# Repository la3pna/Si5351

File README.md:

Si5351
======

Si5351 things

Cadsoft eagle shematics and board layout for the Si5351A backpack. 

Load ATmega32U4 with Arduino bootloader to upload via USB. 

Boards avaible at https://oshpark.com/shared_projects/lqFvJlVT

Mounting tips:
The LCD is supposed to go on the microcontroller side. mount the large components like SMB connectors, crystal (if hole mounted) and pot on the backside of the board.

Arduino pinout:

D0    ENCODER A (Interrupt)

D1    ENCODER b (Interrupt)

D2    I2C SDA to Si5351A

D3    I2C SCI to Si5351A

D4    Extra

D5    Extra

D6    LCD D7

D7    ENCODER SWITCH (Interrupt)

D8    LCD D6

D9    LCD D5

D10   LCD D4

D11   LCD Enable

D12   LCD RS

D13   External LED

None of the analog pins are connected.

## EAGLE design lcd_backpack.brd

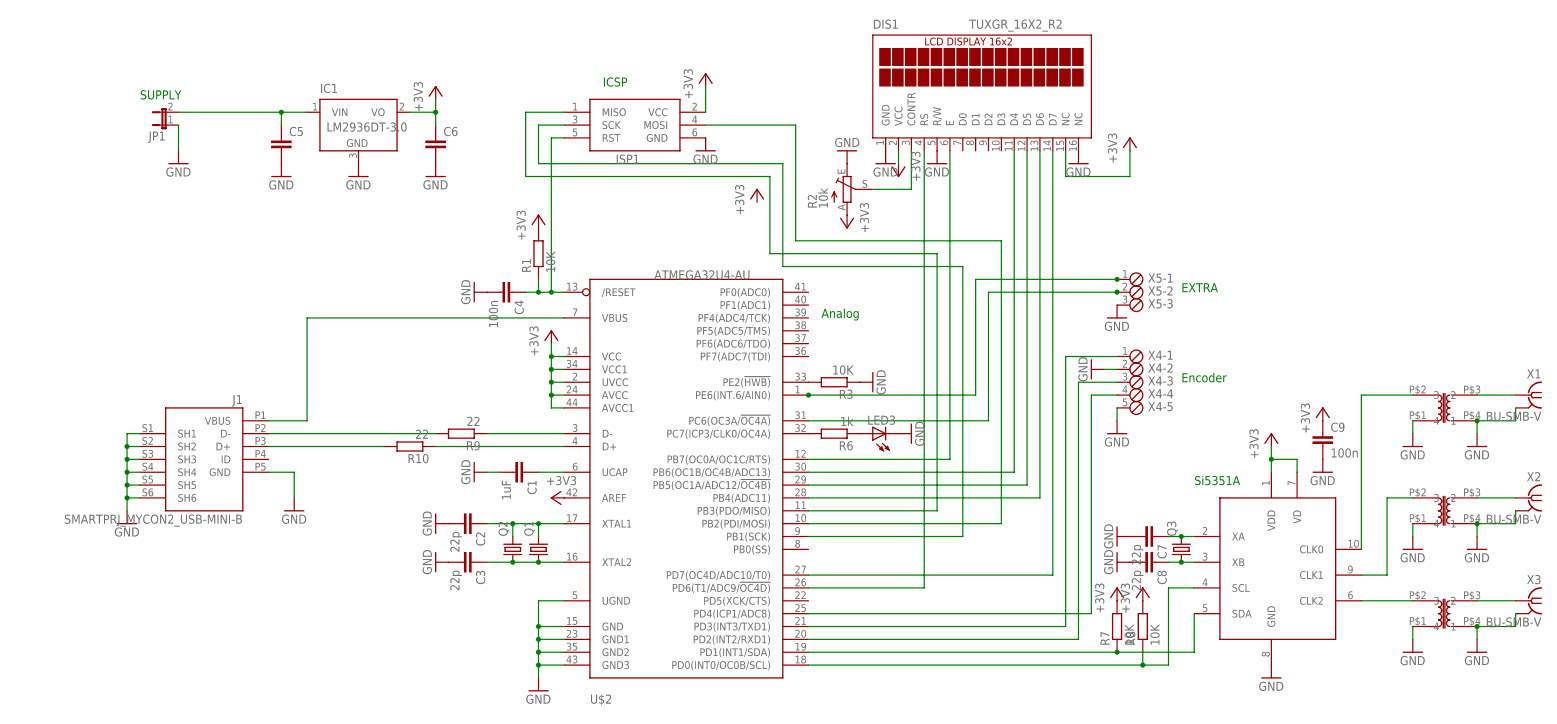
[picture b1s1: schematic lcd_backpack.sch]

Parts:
C1: 1uF; C0805
C2, C3, C7, C8: 22p; C0805
C4, C9: 100n; C0805
C5, C6: C-EUC0805; C0805
DIS1: TUXGR_16X2_R2
IC1: LM2936DT-3.0; TO252
ISP1: AVRISP-6; AVRISP
J1: SMARTPRJ_MYCON2_USB-MINI-B; SMARTPRJ_CON2_USB_MICRO_B_AT
JP1: JUMPER-2PTH_LOCK; 1X02_LOCK
LED3: LED3MM
Q1: CRYSTALHC49UP; HC49UP
Q2: CRYSTALHC49U-V; HC49U-V
Q3: CRYSTALCTS406; CTS406
R1, R3, R7, R8: 10K; M0805
R2: 10k; B25P
R6: 1k; M0805
R9, R10: 22; M0805
TR1, TR2, TR3: FT2402_TRAFO; 2402_TRAFO
U$1: SI5351; MSOP10
U$2: ATMEGA32U4-AU; TQFP44
X1, X2, X3: BU-SMB-V
X4: MPT5; 5POL254
X5: MPT3; 3POL254

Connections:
+3V3: C6.1, C9.1, DIS1.2 (VCC), DIS1.15 (NC), IC1.2 (VO), ISP1.2 (VCC), R1.2, R2.A, R7.2, R8.2, U$1.1 (VDD), U$1.7 (VD), U$2.2 (UVCC), U$2.14 (VCC), U$2.24 (AVCC), U$2.34 (VCC1), U$2.42 (AREF), U$2.44 (AVCC1)
GND: C1.2, C2.2, C3.2, C4.2, C5.2, C6.2, C7.2, C8.2, C9.2, DIS1.1 (GND), DIS1.5 (R/W), DIS1.16 (NC), IC1.3 (GND), ISP1.6 (GND), J1.P5 (GND), J1.S1 (SH1), J1.S2 (SH2), J1.S3 (SH3), J1.S4 (SH4), J1.S5 (SH5), J1.S6 (SH6), JP1.1, LED3.K (C), R2.E, R3.1, TR1.P$1 (1), TR1.P$4 (4), TR2.P$1 (1), TR2.P$4 (4), TR3.P$1 (1), TR3.P$4 (4), U$1.8 (GND), U$2.5 (UGND), U$2.15 (GND), U$2.23 (GND1), U$2.35 (GND2), U$2.43 (GND3), X1.2, X1.3 (2), X1.4 (2), X1.5 (2), X2.2, X2.3 (2), X2.4 (2), X2.5 (2), X3.2, X3.3 (2), X3.4 (2), X3.5 (2), X4.2, X4.5, X5.3
unnamed: J1.P3 (D+), R10.2
unnamed: J1.P2 (D-), R9.2
unnamed: J1.P1 (VBUS), U$2.7 (VBUS)
unnamed: DIS1.4 (RS), U$2.26 (PD6(T1/ADC9/!OC4D))
unnamed: C1.1, U$2.6 (UCAP)
unnamed: DIS1.6 (E), U$2.12 (PB7(OC0A/OC1C/RTS))
unnamed: C2.1, Q1.2, Q2.2, U$2.17 (XTAL1)
unnamed: C3.1, Q1.1, Q2.1, U$2.16 (XTAL2)
unnamed: C4.1, ISP1.5 (RST), R1.1, U$2.13 (/RESET)
unnamed: DIS1.3 (CONTR), R2.S
unnamed: DIS1.11 (D4), U$2.30 (PB6(OC1B/OC4B/ADC13))
unnamed: DIS1.12 (D5), U$2.29 (PB5(OC1A/ADC12/!OC4B))
unnamed: DIS1.13 (D6), U$2.28 (PB4(ADC11))
unnamed: DIS1.14 (D7), U$2.27 (PD7(OC4D/ADC10/T0))
unnamed: TR3.P$3 (3), X3.1
unnamed: C5.1, IC1.1 (VIN), JP1.2
unnamed: TR2.P$3 (3), X2.1
unnamed: TR1.P$3 (3), X1.1
unnamed: R8.1, U$1.4 (SCL), U$2.18 (PD0(INT0/OC0B/SCL))
unnamed: R7.1, U$1.5 (SDA), U$2.19 (PD1(INT1/SDA))
unnamed: ISP1.4 (MOSI), U$2.10 (PB2(PDI/MOSI))
unnamed: C8.1, Q3.1, U$1.3 (XB)
unnamed: C7.1, Q3.3 (2), U$1.2 (XA)
unnamed: TR1.P$2 (2), U$1.10 (CLK0)
unnamed: TR2.P$2 (2), U$1.9 (CLK1)
unnamed: TR3.P$2 (2), U$1.6 (CLK2)
unnamed: R3.2, U$2.33 (PE2(!HWB))
unnamed: U$2.20 (PD2(INT2/RXD1)), X4.3
unnamed: U$2.21 (PD3(INT3/TXD1)), X4.1
unnamed: U$2.25 (PD4(ICP1/ADC8)), X4.4
unnamed: U$2.31 (PC6(OC3A/!OC4A)), X5.2
unnamed: U$2.1 (PE6(INT.6/AIN0)), X5.1
unnamed: ISP1.3 (SCK), U$2.9 (PB1(SCK))
unnamed: ISP1.1 (MISO), U$2.11 (PB3(PDO/MISO))
unnamed: R6.2, U$2.32 (PC7(ICP3/CLK0/OC4A))
unnamed: LED3.A, R6.1
unnamed: R9.1, U$2.3 (D-)
unnamed: R10.1, U$2.4 (D+)

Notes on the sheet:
Encoder
EXTRA
Analog
SUPPLY
ICSP
Si5351A

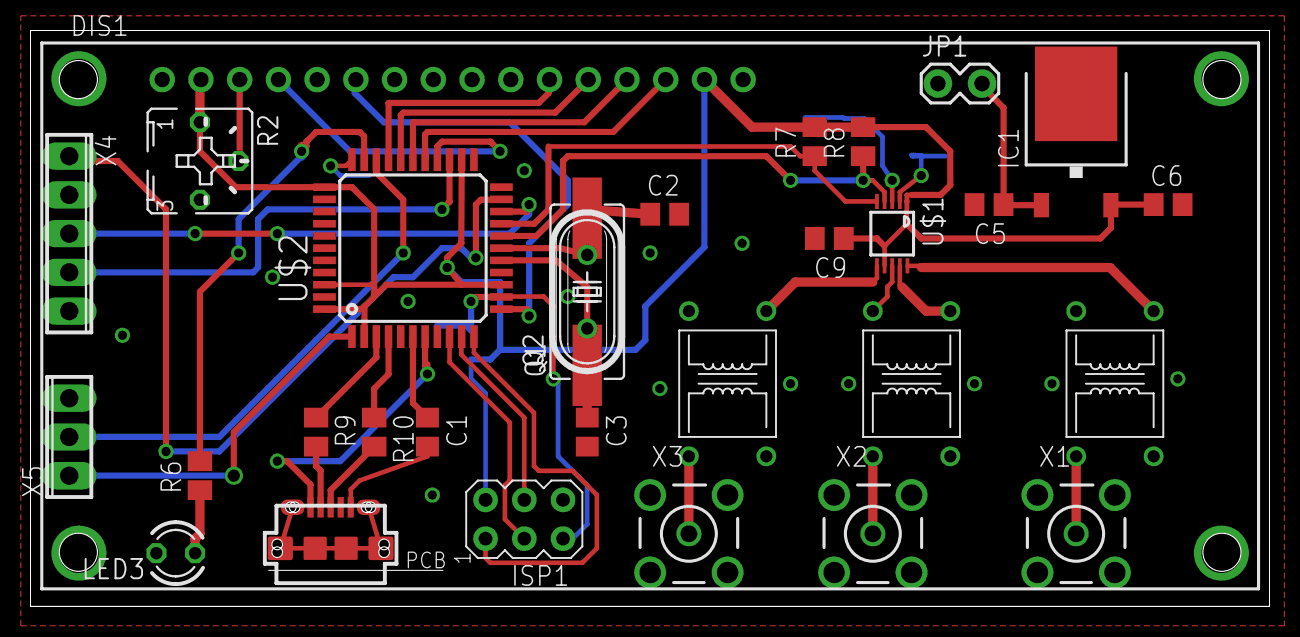
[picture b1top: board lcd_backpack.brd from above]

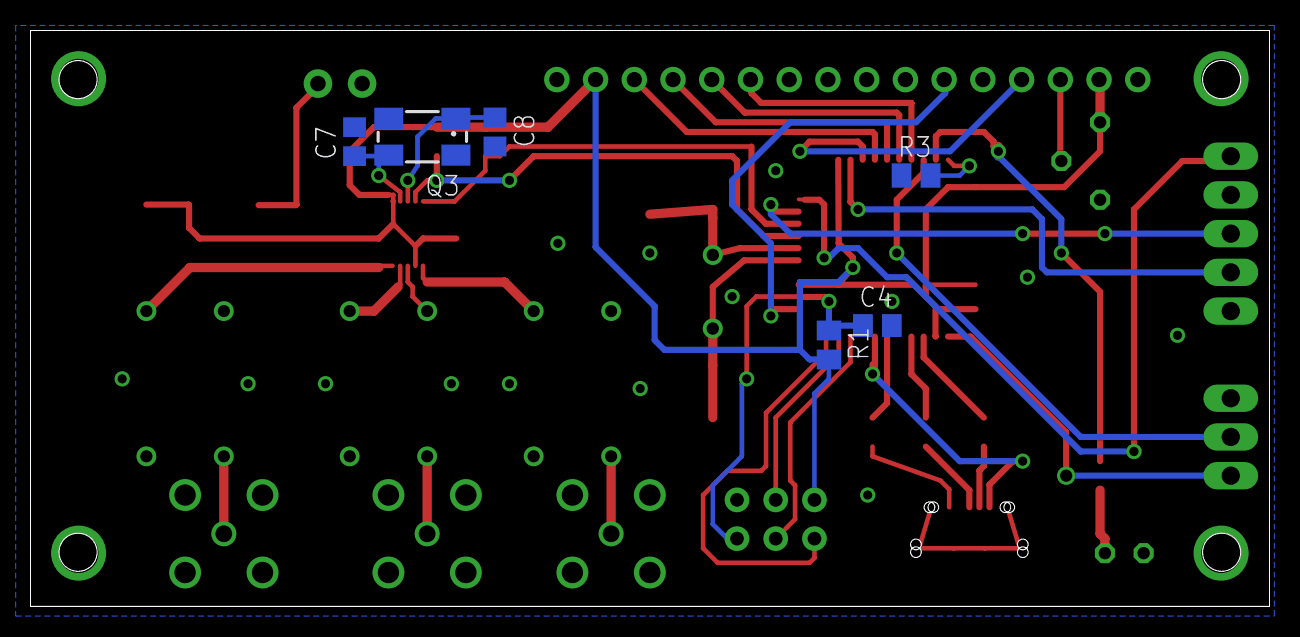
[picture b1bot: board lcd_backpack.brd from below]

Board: 2 copper layers, 81.3 x 37.8 mm, 36 parts (6 on the bottom side), 40 nets.

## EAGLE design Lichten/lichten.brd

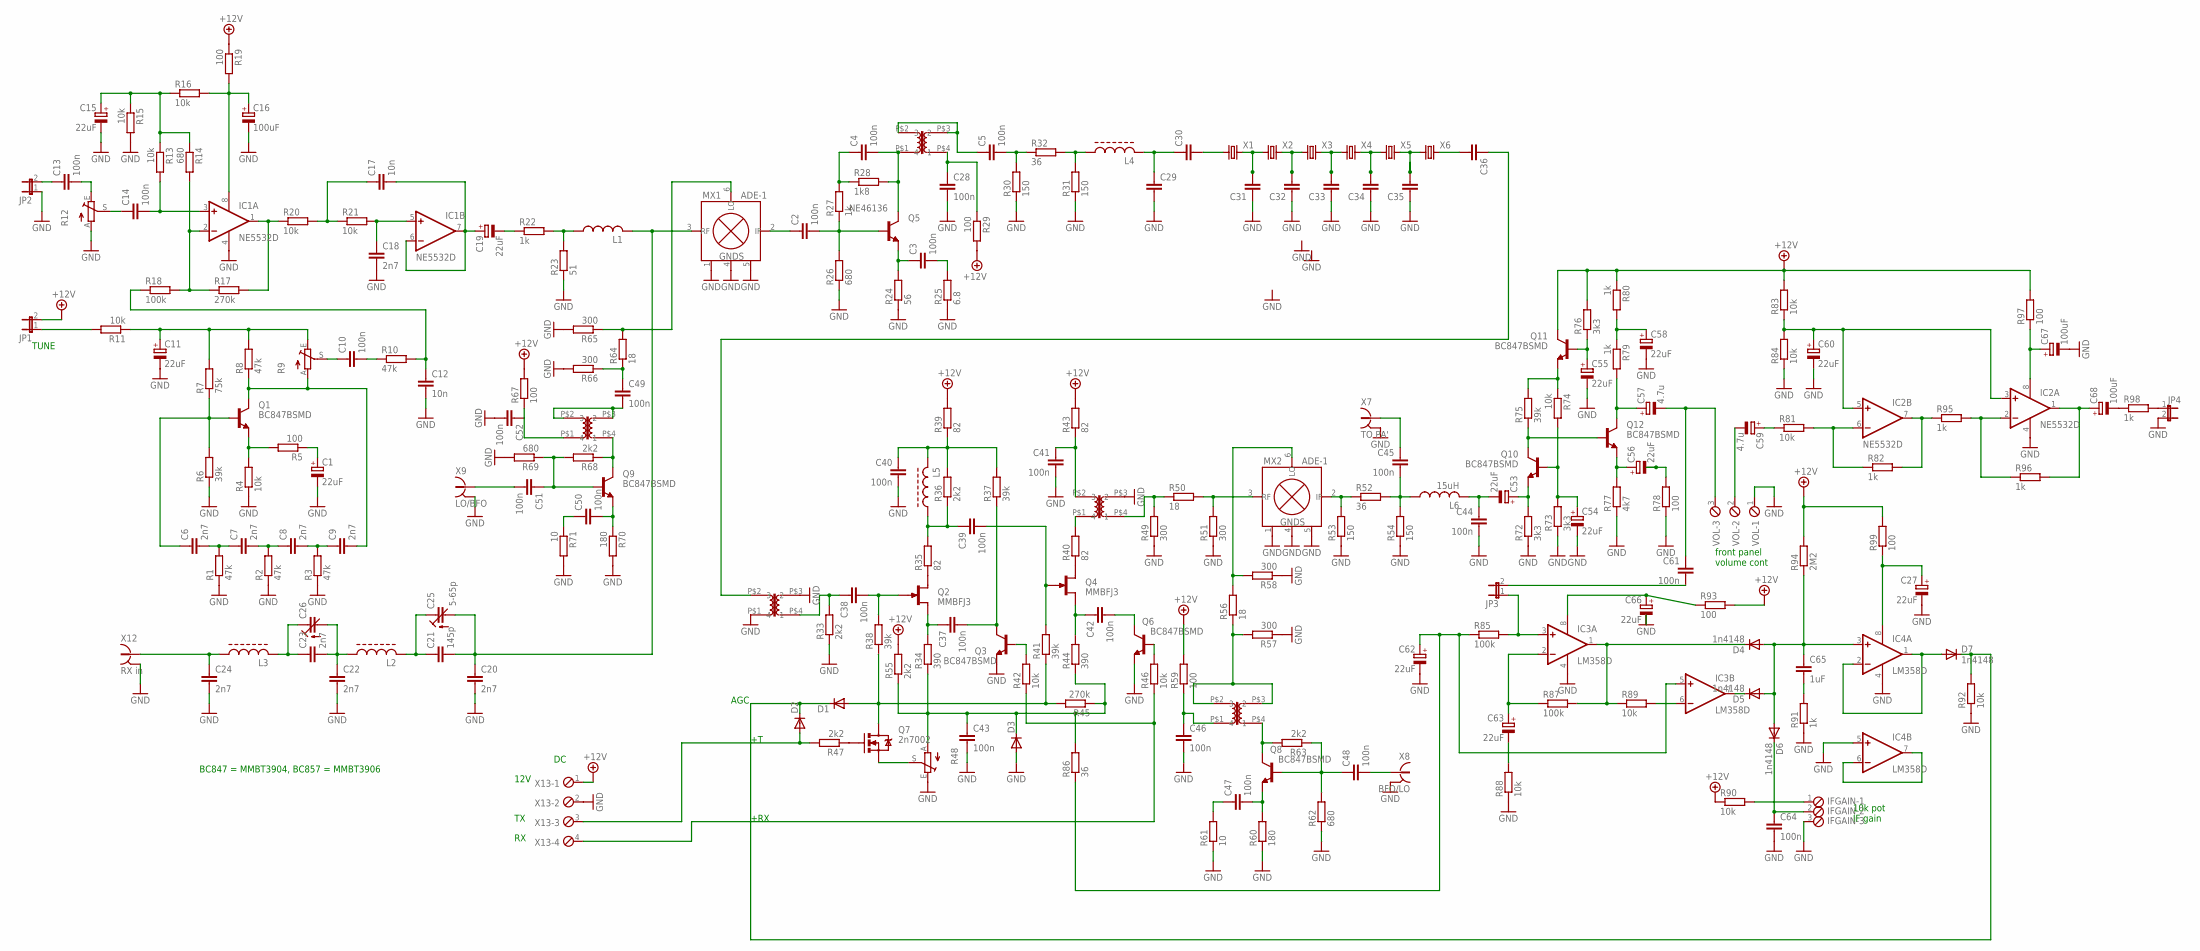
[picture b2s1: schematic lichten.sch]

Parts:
C1, C11, C15, C19, C27, C53, C54, C55, C56, C58, C60, C62, C63, C66: 22uF; PANASONIC_B
C2, C3, C4, C5, C10, C13, C14, C28, C37, C38, C39, C40, C41, C42, C43, C44, C45, C46, C47, C48, C49, C50, C51, C52, C61, C64: 100n; C1206K
C6, C7, C8, C9, C18, C20, C22, C23, C24: 2n7; C1206K
C12, C17: 10n; C1206K
C16, C67, C68: 100uF; PANASONIC_B
C21: 145p; C1206K
C25: 5-65p; CTRIM3050.505
C26: C-TRIMM3050.505; CTRIM3050.505
C29, C30, C31, C32, C33, C34, C35, C36: C-EUC1206K; C1206K
C57, C59: 4.7u; PANASONIC_B
C65: 1uF; C1206K
D1, D2, D3: DIODE-SOD80C; SOD80C
D4, D5, D6, D7: 1n4148; SOD80C
IC1, IC2: NE5532D; SO08
IC3, IC4: LM358D; SO08
IFGAIN: MPT3; 3POL254
JP1, JP2, JP3, JP4: JP1E; JP1
L1: L-US6000-XXX-RC; 6000-XXXX-RC
L2, L3, L4, L5: L-T37-UP
L6: 15uH; 6000-XXXX-RC
MX1, MX2: ADE-1; CD636
Q1, Q3, Q6, Q8, Q9, Q10, Q11, Q12: BC847BSMD; SOT23
Q2, Q4: MMBFJ3; SOT23
Q5: NE46136; SOT89-BCE
Q7: 2n7002; SOT23
R1, R2, R3, R8, R10: 47k; M1206
R4, R11, R13, R15, R16, R20, R21, R42, R46, R74, R81, R83, R84, R88, R89, R90, R92: 10k; M1206
R5, R19, R29, R59, R67, R78, R93, R97, R99: 100; M1206
R6, R37, R38, R41, R75: 39k; M1206
R7: 75k; M1206
R9, R12, R48: TRIM_EU-B25P; B25P
R14, R26, R62, R69: 680; M1206
R17, R45: 270k; M1206
R18, R85, R87: 100k; M1206
R22, R27, R79, R80, R82, R91, R95, R96, R98: 1k; M1206
R23: 51; M1206
R24: 56; M1206
R25: 6.8; M1206
R28: 1k8; M1206
R30, R31, R53, R54: 150; M1206
R32, R52, R86: 36; M1206
R33, R36, R47, R55, R63, R68: 2k2; M1206
R34, R44: 390; M1206
R35, R39, R40, R43: 82; M1206
R49, R51, R57, R58, R65, R66: 300; M1206
R50, R56, R64: 18; M1206
R60, R70: 180; M1206
R61, R71: 10; M1206
R72, R73, R76: 3k3; M1206
R77: 4k7; M1206
R94: 2M2; M1206
TR1, TR2, TR3, TR4, TR5: FT2402_TRAFO; 2402_TRAFO
VOL: MPT3; 3POL254
X1, X2, X3, X4, X5, X6: CRYSTALHC49S; HC49/S
X7: TO PA'; ST-SMB-V
X8: BFO/LO; ST-SMB-V
X9: LO/BFO; ST-SMB-V
X12: RX in; ST-SMB-V
X13: MPT4; 4POL254

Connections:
+12V: JP1.2, Q11.3 (C), R19.1, R29.2, R39.2, R43.2, R55.2, R59.2, R67.2, R76.2, R80.1, R83.2, R90.1, R93.2, R94.2, R97.2, R99.2, X13.1
GND: C1.-, C11.-, C12.2, C15.-, C16.-, C18.2, C20.2, C22.2, C24.2, C27.-, C28.2, C29.2, C31.1, C32.1, C33.1, C34.1, C35.1, C40.2, C41.2, C43.2, C44.2, C46.2, C52.2, C54.-, C55.-, C58.-, C60.-, C62.-, C64.2, C66.-, C67.-, D3.A, IC1.4 (V-), IC2.4 (V-), IC3.4 (V-), IC4.4 (V-), IC4.5 (+IN), IFGAIN.3, JP2.1, JP4.2, MX1.1 (GND), MX1.4 (GND), MX1.5 (GND), MX2.1 (GND), MX2.4 (GND), MX2.5 (GND), Q3.2 (E), Q6.2 (E), R1.1, R2.1, R3.1, R4.1, R6.1, R12.A, R15.2, R23.1, R24.1, R25.1, R26.1, R30.1, R31.1, R33.1, R48.E, R49.1, R51.1, R53.1, R54.1, R57.1, R58.1, R60.1, R61.1, R62.1, R65.2, R66.2, R69.2, R70.2, R71.2, R72.1, R73.1, R77.1, R78.1, R84.1, R88.1, R91.1, R92.1, TR2.P$1 (1), TR2.P$3 (3), TR3.P$3 (3), VOL.1, X7.2, X7.3 (2), X7.4 (2), X7.5 (2), X8.2, X8.3 (2), X8.4 (2), X8.5 (2), X9.2, X9.3 (2), X9.4 (2), X9.5 (2), X12.2, X12.3 (2), X12.4 (2), X12.5 (2), X13.2
unnamed: C20.1, C21.2, C25.2 (A), L1.2, MX1.3 (RF)
unnamed: C21.1, C25.1 (E), L2.2
unnamed: C22.1, C23.2, C26.2 (A), L2.1
unnamed: Q1.2 (E), R4.2, R5.2
unnamed: C1.+, R5.1
unnamed: C9.2, Q1.3 (C), R8.1, R9.A
unnamed: C8.2, C9.1, R3.2
unnamed: C7.2, C8.1, R2.2
unnamed: C6.2, C7.1, R1.2
unnamed: C6.1, Q1.1 (B), R6.2, R7.1
unnamed: C11.+, R7.2, R8.2, R9.E, R11.1
unnamed: C10.1, R9.S
unnamed: C10.2, R10.1
unnamed: C14.1, R12.S
unnamed: JP1.1, R11.2
unnamed: C12.1, R10.2, R18.1
unnamed: C13.2, R12.E
unnamed: C14.2, IC1.3 (+IN), R13.2
unnamed: C15.+, R13.1, R14.1, R15.1, R16.1
unnamed: IC1.2 (-IN), R14.2, R17.1, R18.2
unnamed: C23.1, C26.1 (E), L3.2
unnamed: IC1.1 (OUT), R17.2, R20.1
unnamed: C30.2, X1.1
unnamed: C13.1, JP2.2
unnamed: C24.1, L3.1, X12.1
unnamed: C2.1, MX1.2 (IF)
unnamed: C16.+, IC1.8 (V+), R16.2, R19.2
unnamed: C17.1, R20.2, R21.1
unnamed: C18.1, IC1.5 (+IN), R21.2
unnamed: C17.2, C19.+, IC1.6 (-IN), IC1.7 (OUT)
unnamed: C2.2, Q5.B, R26.2, R27.1
unnamed: C19.-, R22.1
unnamed: L1.1, R22.2, R23.2
unnamed: C3.1, Q5.E, R24.2
unnamed: C4.2, Q5.C, R28.2, TR1.P$1 (1)
unnamed: C4.1, R27.2, R28.1
unnamed: C5.1, TR1.P$2 (2), TR1.P$3 (3)
unnamed: C3.2, R25.2
unnamed: C28.1, R29.1, TR1.P$4 (4)
unnamed: C5.2, R30.2, R32.1
unnamed: L4.1, R31.2, R32.2
unnamed: C29.1, C30.1, L4.2
unnamed: C31.2, X1.2, X2.1
unnamed: C32.2, X2.2, X3.1
unnamed: C33.2, X3.2, X4.1
unnamed: C34.2, X4.2, X5.1
unnamed: C35.2, X5.2, X6.1
unnamed: C38.1, R33.2, TR2.P$4 (4)
unnamed: C36.2, X6.2
unnamed: C37.1, Q2.2 (S), R34.2
unnamed: Q2.1 (D), R35.1
unnamed: C39.1, L5.1, R35.2, R36.1
unnamed: C38.2, Q2.3 (G), R38.2
unnamed: C40.1, L5.2, R36.2, R37.2, R39.1
unnamed: C37.2, Q3.3 (C), R37.1
unnamed: C36.1, TR2.P$2 (2)
unnamed: C39.2, Q4.3 (G), R41.2
unnamed: Q4.1 (D), R40.1
unnamed: Q3.1 (B), R42.2
unnamed: D1.A, Q7.3 (D), R38.1, R41.1, R45.2
unnamed: R40.2, TR3.P$1 (1)
unnamed: C41.1, R43.1, TR3.P$2 (2)
unnamed: C42.1, Q4.2 (S), R44.2
unnamed: C42.2, Q6.3 (C)
unnamed: C68.+, IC2.1 (OUT), R96.2
unnamed: C43.1, D3.C, R34.1, R44.1, R45.1, R48.A, R55.1, R86.2
unnamed: Q6.1 (B), R46.2
unnamed: R42.1, R46.1, X13.4
unnamed: Q7.1 (G), R47.1
unnamed: D2.A, R47.2, X13.3
unnamed: Q7.2 (S), R48.S
unnamed: R49.2, R50.1, TR3.P$4 (4)
unnamed: MX2.3 (RF), R50.2, R51.2
unnamed: MX2.2 (IF), R52.1, R53.2
unnamed: C45.2, L6.1, R52.2, R54.2
unnamed: C44.1, C53.-, L6.2
unnamed: C45.1, X7.1
unnamed: C54.+, Q10.1 (B), R73.2, R74.2
unnamed: MX2.6 (LO), R56.2, R58.2
unnamed: R56.1, R57.2, TR4.P$2 (2), TR4.P$3 (3)
unnamed: Q8.3 (C), R63.2, TR4.P$4 (4)
unnamed: C46.1, R59.1, TR4.P$1 (1)
unnamed: C47.2, Q8.2 (E), R60.2
unnamed: C48.1, Q8.1 (B), R62.2, R63.1
unnamed: C47.1, R61.2
unnamed: C48.2, X8.1
unnamed: Q9.3 (C), R68.1, TR5.P$4 (4)
unnamed: C49.2, TR5.P$2 (2), TR5.P$3 (3)
unnamed: C49.1, R64.1, R66.1
unnamed: MX1.6 (LO), R64.2, R65.1
unnamed: C52.1, R67.1, TR5.P$1 (1)
unnamed: C51.1, Q9.1 (B), R68.2, R69.1
unnamed: C50.1, R71.1
unnamed: C50.2, Q9.2 (E), R70.1
unnamed: C51.2, X9.1
unnamed: C53.+, Q10.2 (E), R72.2
unnamed: C56.-, R78.2
unnamed: Q10.3 (C), Q12.1 (B), R75.1
unnamed: Q11.2 (E), R74.1, R75.2
unnamed: C55.+, Q11.1 (B), R76.1
unnamed: C67.+, IC2.8 (V+), R97.1
unnamed: C56.+, Q12.2 (E), R77.2
unnamed: C57.+, Q12.3 (C), R79.2
unnamed: C58.+, R79.1, R80.2
unnamed: C57.-, C61.1, VOL.3
unnamed: IC2.6 (-IN), R81.2, R82.1
unnamed: C59.-, VOL.2
unnamed: IC2.7 (OUT), R82.2, R95.1
unnamed: C59.+, R81.1
unnamed: C60.+, IC2.3 (+IN), IC2.5 (+IN), R83.1, R84.2
unnamed: C62.+, IC3.5 (+IN), R85.1, R86.1
unnamed: C63.-, R88.2
unnamed: C61.2, JP3.2
unnamed: C63.+, IC3.2 (-IN), R87.1
unnamed: D4.C, IC3.1 (OUT), R87.2, R89.1
unnamed: IC3.6 (-IN), R89.2
unnamed: C68.-, R98.1
unnamed: D5.C, IC3.7 (OUT)
unnamed: C65.1, D4.A, D5.A, D6.A, IC4.3 (+IN), R94.1
unnamed: IFGAIN.1, R90.2
unnamed: C64.1, D6.C, IFGAIN.2
unnamed: C65.2, R91.2
unnamed: D7.A, IC4.1 (OUT), IC4.2 (-IN)
unnamed: D1.C, D2.C, D7.C, R92.2
unnamed: C66.+, R93.1
unnamed: IC4.6 (-IN), IC4.7 (OUT)
unnamed: IC2.2 (-IN), R95.2, R96.1
unnamed: IC3.3 (+IN), JP3.1, R85.2
unnamed: JP4.1, R98.2
unnamed: C27.+, IC4.8 (V+), R99.1

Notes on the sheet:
BC847 = MMBT3904, BC857 = MMBT3906
TUNE
+RX
AGC
front panel volume cont
10k pot IF gain
12V

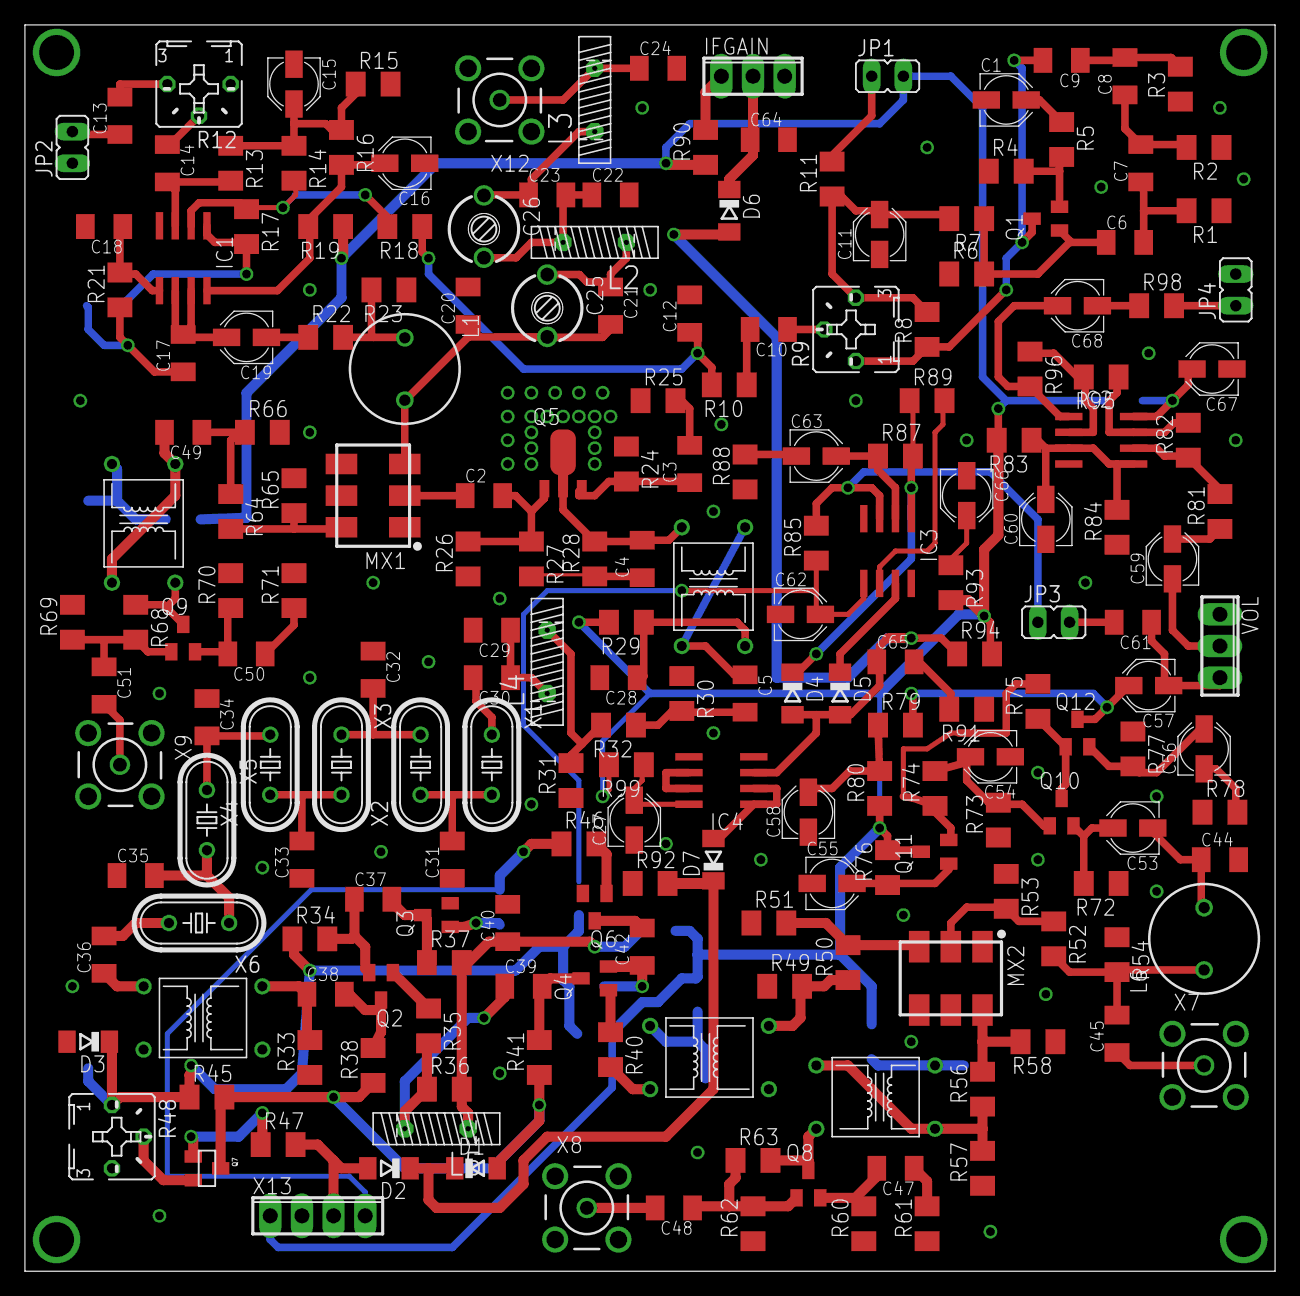
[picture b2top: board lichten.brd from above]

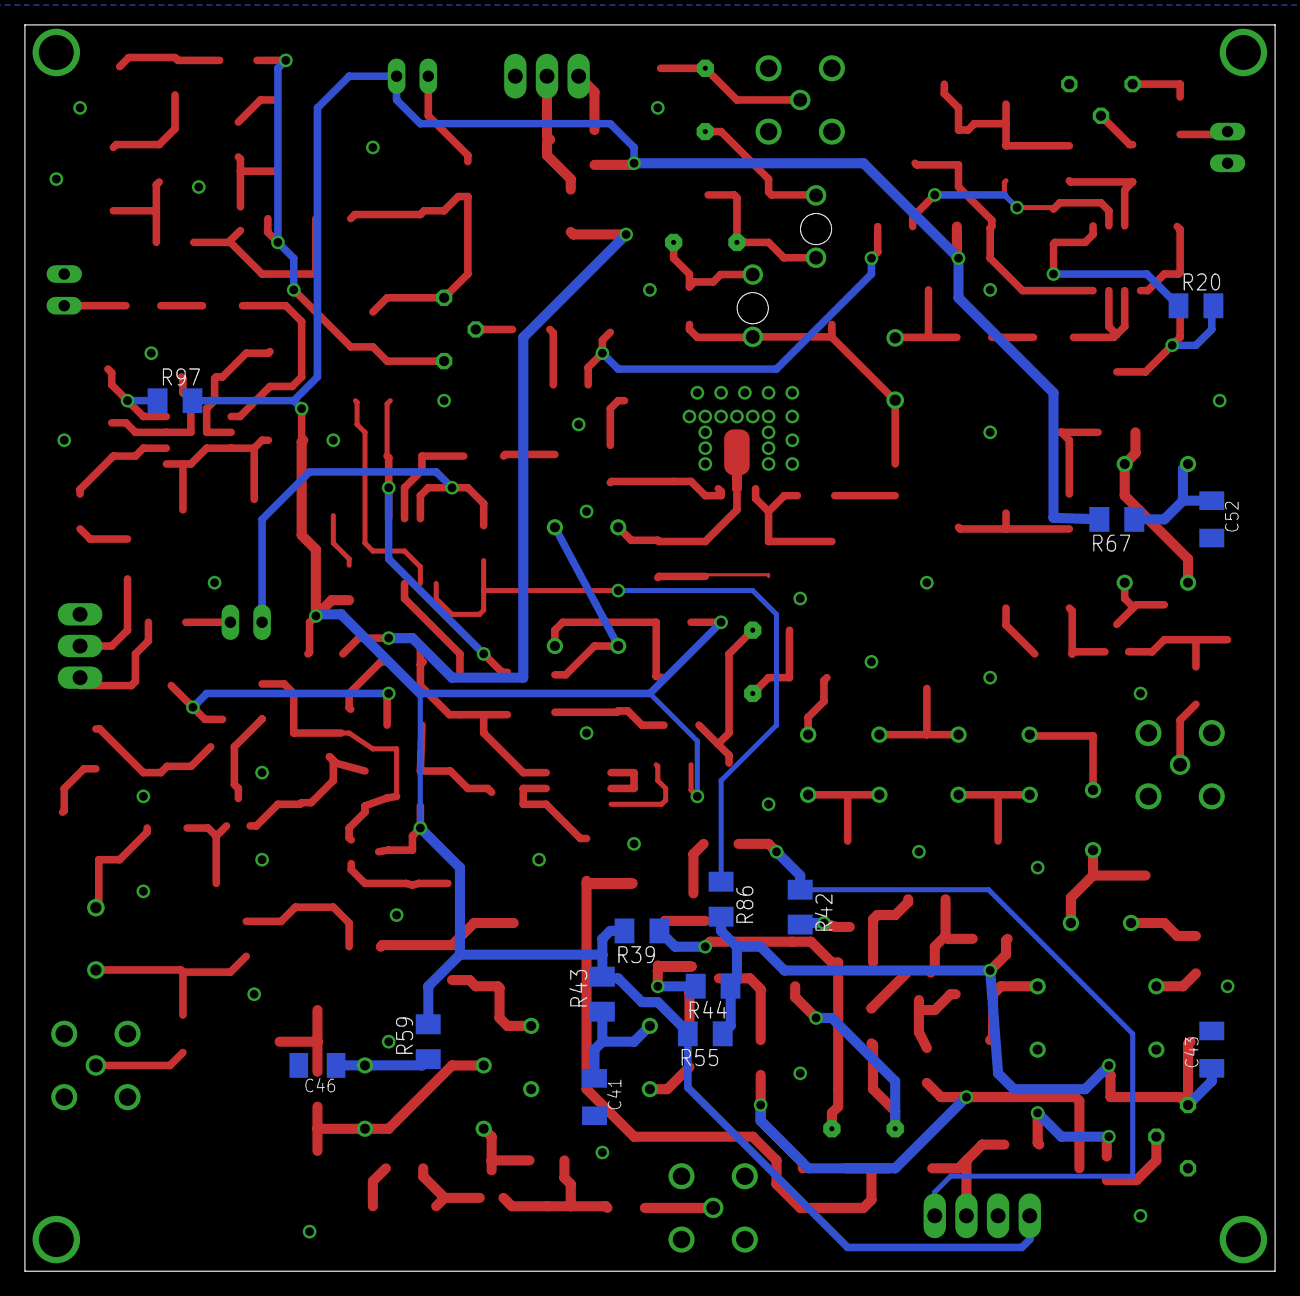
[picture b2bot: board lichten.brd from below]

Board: 2 copper layers, 100.3 x 100.0 mm, 220 parts (14 on the bottom side), 132 nets.

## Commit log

2014-10-29 Start
    Lets start!
2014-10-29 fixed board, added soldermask to vias
2014-10-29 Fixed rendering issue with board
2014-10-31 Lichten added
2014-10-31 pdf's of lichten
2014-10-31 G-code
2014-10-31 gcode
2014-11-02 fixed transformer layout
2014-11-02 g-code and gerber for edited version
2014-11-07 fixed the USB connector to digikey 609-4618-1-nd
2014-11-07 connector and via fix. Closed vias.

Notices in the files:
parts and their libraries:
SparkFun-DiscreteSemi: Licensing: CC v3.0 Share-Alike You are welcome to use this library for commercial purposes.
